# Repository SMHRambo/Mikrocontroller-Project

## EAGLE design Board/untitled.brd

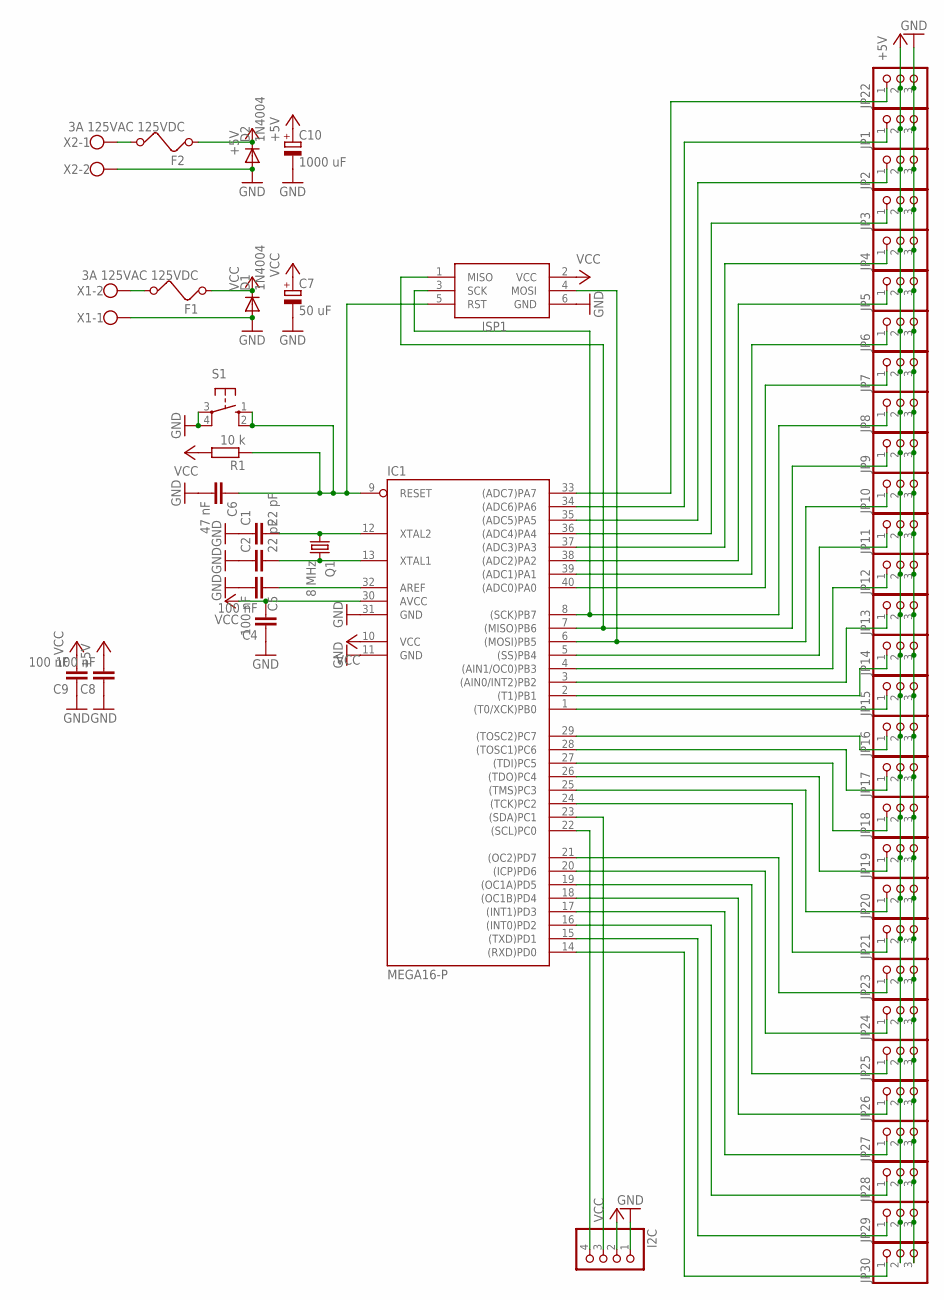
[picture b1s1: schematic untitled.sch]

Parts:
C1, C2: 22 pF; C0805
C4, C5, C8, C9: 100 nF; C0805
C6: 47 nF; C0805
C7: 50 uF; E2-5
C10: 1000 uF; E2-5
D1, D2: 1N4004; DO214AC
F1, F2: 3A 125VAC 125VDC; FUSE
I2C: PINHD-1X4; 1X04
IC1: MEGA16-P; DIL40
ISP1: AVRISP-6; AVRISP
JP1, JP2, JP3, JP4, JP5, JP6, JP7, JP8, JP9, JP10, JP11, JP12, JP13, JP14, JP15, JP16, JP17, JP18, JP19, JP20, JP21, JP22, JP23, JP24, JP25, JP26, JP27, JP28, JP29, JP30: PINHD-1X3; 1X03
Q1: 8 MHz; HC49/S
R1: 10 k; R0805
S1: 10-XX; B3F-10XX
X1, X2: W237-102

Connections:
+5V: C8.2, C10.+, D2.C, F2.1, JP1.2, JP2.2, JP3.2, JP4.2, JP5.2, JP6.2, JP7.2, JP8.2, JP9.2, JP10.2, JP11.2, JP12.2, JP13.2, JP14.2, JP15.2, JP16.2, JP17.2, JP18.2, JP19.2, JP20.2, JP21.2, JP22.2, JP23.2, JP24.2, JP25.2, JP26.2, JP27.2, JP28.2, JP29.2, JP30.2
GND: C1.1, C2.1, C4.1, C5.2, C6.2, C7.-, C8.1, C9.1, C10.-, D1.A, D2.A, I2C.1, IC1.11 (GND), IC1.31 (GND), ISP1.6 (GND), JP1.3, JP2.3, JP3.3, JP4.3, JP5.3, JP6.3, JP7.3, JP8.3, JP9.3, JP10.3, JP11.3, JP12.3, JP13.3, JP14.3, JP15.3, JP16.3, JP17.3, JP18.3, JP19.3, JP20.3, JP21.3, JP22.3, JP23.3, JP24.3, JP25.3, JP26.3, JP27.3, JP28.3, JP29.3, JP30.3, S1.3, S1.4 (P1), X1.1, X2.2
unnamed: C1.2, IC1.12 (XTAL2), Q1.1
unnamed: C2.2, IC1.13 (XTAL1), Q1.2
unnamed: C5.1, IC1.32 (AREF)
unnamed: F1.2, X1.2
unnamed: IC1.8 ((SCK)PB7), ISP1.3 (SCK), JP8.1
unnamed: IC1.6 ((MOSI)PB5), ISP1.4 (MOSI), JP10.1
unnamed: C6.1, IC1.9 (RESET), ISP1.5 (RST), R1.1, S1.1 (S), S1.2 (S1)
unnamed: IC1.1 ((T0/XCK)PB0), JP15.1
unnamed: I2C.4, IC1.22 ((SCL)PC0)
unnamed: F2.2, X2.1
unnamed: IC1.36 ((ADC4)PA4), JP3.1
unnamed: IC1.33 ((ADC7)PA7), JP22.1
unnamed: IC1.39 ((ADC1)PA1), JP6.1
unnamed: I2C.3, IC1.23 ((SDA)PC1)
unnamed: IC1.28 ((TOSC1)PC6), JP17.1
unnamed: IC1.7 ((MISO)PB6), ISP1.1 (MISO), JP9.1
unnamed: IC1.27 ((TDI)PC5), JP18.1
unnamed: IC1.40 ((ADC0)PA0), JP7.1
unnamed: IC1.4 ((AIN1/OC0)PB3), JP12.1
unnamed: IC1.29 ((TOSC2)PC7), JP16.1
unnamed: IC1.2 ((T1)PB1), JP14.1
unnamed: IC1.3 ((AIN0/INT2)PB2), JP13.1
unnamed: IC1.37 ((ADC3)PA3), JP4.1
unnamed: IC1.5 ((SS)PB4), JP11.1
unnamed: IC1.38 ((ADC2)PA2), JP5.1
unnamed: IC1.35 ((ADC5)PA5), JP2.1
unnamed: IC1.34 ((ADC6)PA6), JP1.1
unnamed: IC1.26 ((TDO)PC4), JP19.1
unnamed: IC1.25 ((TMS)PC3), JP20.1
unnamed: IC1.24 ((TCK)PC2), JP21.1
unnamed: IC1.21 ((OC2)PD7), JP23.1
unnamed: IC1.20 ((ICP)PD6), JP24.1
unnamed: IC1.19 ((OC1A)PD5), JP25.1
unnamed: IC1.18 ((OC1B)PD4), JP26.1
unnamed: IC1.17 ((INT1)PD3), JP27.1
unnamed: IC1.16 ((INT0)PD2), JP28.1
unnamed: IC1.15 ((TXD)PD1), JP29.1
unnamed: IC1.14 ((RXD)PD0), JP30.1
VCC: C4.2, C7.+, C9.2, D1.C, F1.1, I2C.2, IC1.10 (VCC), IC1.30 (AVCC), ISP1.2 (VCC), R1.2

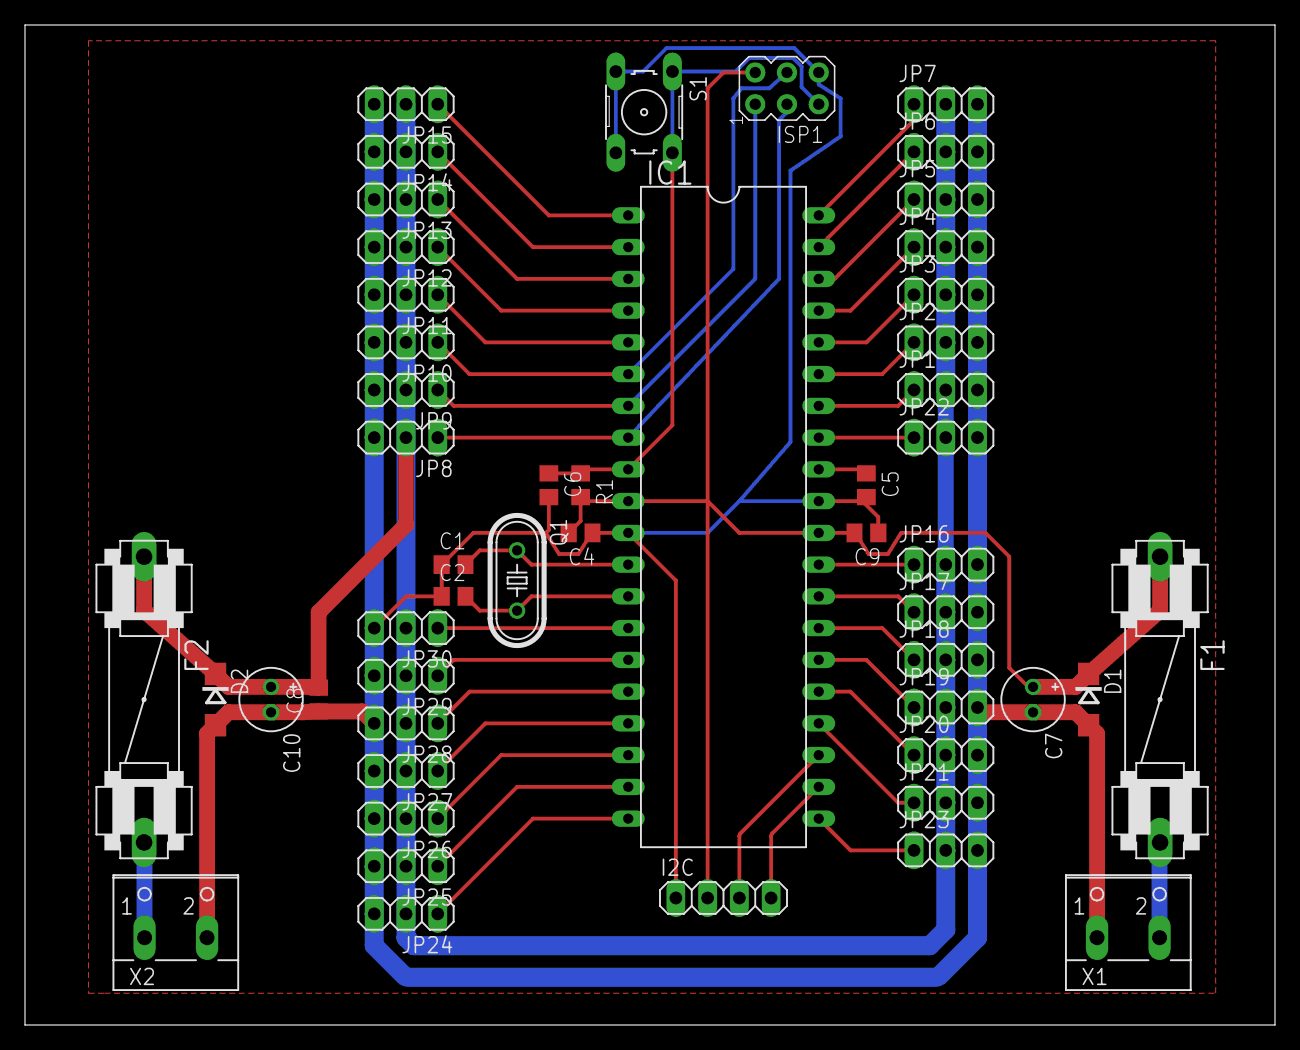
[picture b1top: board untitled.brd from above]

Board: 2 copper layers, 100.0 x 80.0 mm, 51 parts (0 on the bottom side), 41 nets.

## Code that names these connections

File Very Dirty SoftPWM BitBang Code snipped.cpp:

#include <util/twi.h>
#include <avr/interrupt.h>
#include <stdint.h>
#include <avr/io.h>

/* PORTA */
#define PA7     7
#define PA6     6
#define PA5     5
#define PA4     4
#define PA3     3
#define PA2     2
#define PA1     1
#define PA0     0

/* DDRA */
#define DDA7    7
#define DDA6    6
#define DDA5    5
#define DDA4    4
#define DDA3    3
#define DDA2    2
#define DDA1    1
#define DDA0    0

/* PINA */
#define PINA7   7
#define PINA6   6
#define PINA5   5
#define PINA4   4
#define PINA3   3
#define PINA2   2
#define PINA1   1
#define PINA0   0

/* PORTB */
#define PB7     7
#define PB6     6
#define PB5     5
#define PB4     4
#define PB3     3
#define PB2     2
#define PB1     1
#define PB0     0

/* DDRB */
#define DDB7    7
#define DDB6    6
#define DDB5    5
#define DDB4    4
#define DDB3    3
#define DDB2    2
#define DDB1    1
#define DDB0    0

/* PINB */
#define PINB7   7
#define PINB6   6
#define PINB5   5
#define PINB4   4
#define PINB3   3
#define PINB2   2
#define PINB1   1
#define PINB0   0

/* PORTC */
#define PC7     7
#define PC6     6
#define PC5     5
#define PC4     4
#define PC3     3
#define PC2     2
#define PC1     1
#define PC0     0

/* DDRC */
#define DDC7    7
#define DDC6    6
#define DDC5    5
#define DDC4    4
#define DDC3    3
#define DDC2    2
#define DDC1    1
#define DDC0    0

/* PINC */
#define PINC7   7
#define PINC6   6
#define PINC5   5
#define PINC4   4
#define PINC3   3
#define PINC2   2
#define PINC1   1
#define PINC0   0

/* PORTD */
#define PD7     7
#define PD6     6
#define PD5     5
#define PD4     4
#define PD3     3
#define PD2     2
#define PD1     1
#define PD0     0

/* DDRD */
#define DDD7    7
#define DDD6    6
#define DDD5    5
#define DDD4    4
#define DDD3    3
#define DDD2    2
#define DDD1    1
#define DDD0    0

/* PIND */
#define PIND7   7
#define PIND6   6
#define PIND5   5
#define PIND4   4
#define PIND3   3
#define PIND2   2
#define PIND1   1
#define PIND0   0

uint8_t PORTA;
uint8_t PORTB;
uint8_t PORTC;
uint8_t PORTD;

uint16_t Timer;


uint16_t iChannel[31];

uint16_t pwm_Time = 0;

int main() {

    for(uint8_t i = 0; i < 30; i++)
    {
        iChannel[i] = 1500; //550(350) - 2450(2250)
    }

    iChannel[30] = 20000;

    DDRA |= (1 << PA0);
    DDRA |= (1 << PA1);
    DDRA |= (1 << PA2);
    DDRA |= (1 << PA3);
    DDRA |= (1 << PA4);
    DDRA |= (1 << PA5);
    DDRA |= (1 << PA6);
    DDRA |= (1 << PA7);
    DDRA |= (1 << PA0);
    DDRA |= (1 << PA1);
    DDRA |= (1 << PA2);
    DDRA |= (1 << PA3);
    DDRA |= (1 << PA4);
    DDRA |= (1 << PA5);
    DDRA |= (1 << PA6);
    DDRA |= (1 << PA7);
    DDRA |= (1 << PA0);
    DDRA |= (1 << PA1);
    DDRA |= (1 << PA2);
    DDRA |= (1 << PA3);
    DDRA |= (1 << PA4);
    DDRA |= (1 << PA5);
    DDRA |= (1 << PA6);
    DDRA |= (1 << PA7);
    DDRA |= (1 << PA0);
    DDRA |= (1 << PA1);
    DDRA |= (1 << PA2);
    DDRA |= (1 << PA3);
    DDRA |= (1 << PA4);
    DDRA |= (1 << PA5);
    DDRA |= (1 << PA6);
    DDRA |= (1 << PA7);

    while(true) {
        pwm_Time = Timer;

        if(pwm_Time > iChannel[30])
        {
            PORTA |= (1 << PA0);
            PORTA |= (1 << PA1);
            PORTA |= (1 << PA2);
            PORTA |= (1 << PA3);
            PORTA |= (1 << PA4);
            PORTA |= (1 << PA5);
            PORTA |= (1 << PA6);
            PORTA |= (1 << PA7);
            PORTB |= (1 << PB0);
            PORTB |= (1 << PB1);
            PORTB |= (1 << PB2);
            PORTB |= (1 << PB3);
            PORTB |= (1 << PB4);
            PORTB |= (1 << PB5);
            PORTB |= (1 << PB6);
            PORTB |= (1 << PB7);
            PORTC |= (1 << PC0);
            PORTC |= (1 << PC1);
            PORTC |= (1 << PC2);
            PORTC |= (1 << PC3);
            PORTC |= (1 << PC4);
            PORTC |= (1 << PC5);
            PORTC |= (1 << PC6);
            PORTC |= (1 << PC7);
            PORTD |= (1 << PD0);
            PORTD |= (1 << PD1);
            PORTD |= (1 << PD2);
            PORTD |= (1 << PD3);
            PORTD |= (1 << PD4);
            PORTD |= (1 << PD5);
            PORTD |= (1 << PD6);
            PORTD |= (1 << PD7);
            Timer = 0;
            pwm_Time = 0;
        }

        if(pwm_Time > iChannel[0]) PORTA &= ~(1 << PA0);
        if(pwm_Time > iChannel[1]) PORTA &= ~(1 << PA1);
        if(pwm_Time > iChannel[2]) PORTA &= ~(1 << PA2);
        if(pwm_Time > iChannel[3]) PORTA &= ~(1 << PA3);
        if(pwm_Time > iChannel[4]) PORTA &= ~(1 << PA4);
        if(pwm_Time > iChannel[5]) PORTA &= ~(1 << PA5);
        if(pwm_Time > iChannel[6]) PORTA &= ~(1 << PA6);
        if(pwm_Time > iChannel[7]) PORTA &= ~(1 << PA7);
        if(pwm_Time > iChannel[8]) PORTB &= ~(1 << PB0);
        if(pwm_Time > iChannel[9]) PORTB &= ~(1 << PB1);
        if(pwm_Time > iChannel[10]) PORTB &= ~(1 << PB2);
        if(pwm_Time > iChannel[11]) PORTB &= ~(1 << PB3);
        if(pwm_Time > iChannel[12]) PORTB &= ~(1 << PB4);
        if(pwm_Time > iChannel[13]) PORTB &= ~(1 << PB5);
        if(pwm_Time > iChannel[14]) PORTB &= ~(1 << PB6);
        if(pwm_Time > iChannel[15]) PORTB &= ~(1 << PB7);
        if(pwm_Time > iChannel[16]) PORTC &= ~(1 << PC2);
        if(pwm_Time > iChannel[17]) PORTC &= ~(1 << PC3);
        if(pwm_Time > iChannel[18]) PORTC &= ~(1 << PC4);
        if(pwm_Time > iChannel[19]) PORTC &= ~(1 << PC5);
        if(pwm_Time > iChannel[20]) PORTC &= ~(1 << PC6);
        if(pwm_Time > iChannel[21]) PORTC &= ~(1 << PC7);
        if(pwm_Time > iChannel[22]) PORTD &= ~(1 << PD0);
        if(pwm_Time > iChannel[23]) PORTD &= ~(1 << PD1);
        if(pwm_Time > iChannel[24]) PORTD &= ~(1 << PD2);
        if(pwm_Time > iChannel[25]) PORTD &= ~(1 << PD3);
        if(pwm_Time > iChannel[26]) PORTD &= ~(1 << PD4);
        if(pwm_Time > iChannel[27]) PORTD &= ~(1 << PD5);
        if(pwm_Time > iChannel[28]) PORTD &= ~(1 << PD6);
        if(pwm_Time > iChannel[29]) PORTD &= ~(1 << PD7);
    }

    return 0;
}

void init_twi_slave(uint8_t adr)
{
    TWAR= adr; //Adresse setzen
	TWCR &= ~(1<<TWSTA)|(1<<TWSTO);
	TWCR|= (1<<TWEA) | (1<<TWEN)|(1<<TWIE); 	
	buffer_adr=0xFF;  
	sei();
}

//ACK nach empfangenen Daten senden/ ACK nach gesendeten Daten erwarten
#define TWCR_ACK TWCR = (1<<TWEN)|(1<<TWIE)|(1<<TWINT)|(1<<TWEA)|(0<<TWSTA)|(0<<TWSTO)|(0<<TWWC);  

//NACK nach empfangenen Daten senden/ NACK nach gesendeten Daten erwarten     
#define TWCR_NACK TWCR = (1<<TWEN)|(1<<TWIE)|(1<<TWINT)|(0<<TWEA)|(0<<TWSTA)|(0<<TWSTO)|(0<<TWWC);

//switch to the non adressed slave mode...
#define TWCR_RESET TWCR = (1<<TWEN)|(1<<TWIE)|(1<<TWINT)|(1<<TWEA)|(0<<TWSTA)|(1<<TWSTO)|(0<<TWWC);  

ISR (TWI_vect) {
    uint8_t data=0;

    switch (TW_STATUS) {

        case TW_SR_SLA_ACK:
            buffer_adr = 0xFF;
            TWCR_ACK;
            break;
        
        case TW_SR_DATA_ACK:
            data = TWDR;
            if (buffer_adr == 0xFF) {
                if(data < 63) {
                    buffer_adr = data;
                } else {
                    buffer_adr = 0;
                }				
                TWCR_ACK;
            } else {
                if(buffer_adr < 63) {
                    iChannel[buffer_adr++] = data;
                }
                TWCR_ACK;	
            }
            break;

        case TW_ST_SLA_ACK:
        case TW_ST_DATA_ACK: //0xB8 Slave Transmitter, Daten wurden angefordert
            if (buffer_adr == 0xFF) {
                buffer_adr = 0;
            }	
                
            if(buffer_adr < 63) {
                TWDR = iChannel[buffer_adr];
                buffer_adr++;
            } else {
                TWDR = 0;
            }
            TWCR_ACK;
            break;

        case TW_SR_STOP:
            TWCR_ACK;
            break;

        case TW_ST_DATA_NACK:
        case TW_SR_DATA_NACK:
        case TW_ST_LAST_DATA:
        default: 	
            TWCR_RESET;
            break;
    }
}

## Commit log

2017-11-01 Add Eagle Board data
2017-11-01 Add Atmel AVR Studio Project with Firmwaredata
2017-12-03 Seperate power input fot uC and servos. Change uC rom QFP to DIP for better repair process.
2017-12-03 Create new board
2018-01-12 Change alot of code. Add TWI(i2c) code
2018-01-12 Code from other projects very old i2c c code translate into asm
2018-01-12 Hauptsächlich TODO abgearbeitet Funktionen optimiert und vereinheitlicht Register müssen für die Timer_int noch auf dem stack abgelegt werden. Im groben fehlt nur noch die update funktion.
2018-01-14 Neuschreiben der PWM Update function bei der hälfte
